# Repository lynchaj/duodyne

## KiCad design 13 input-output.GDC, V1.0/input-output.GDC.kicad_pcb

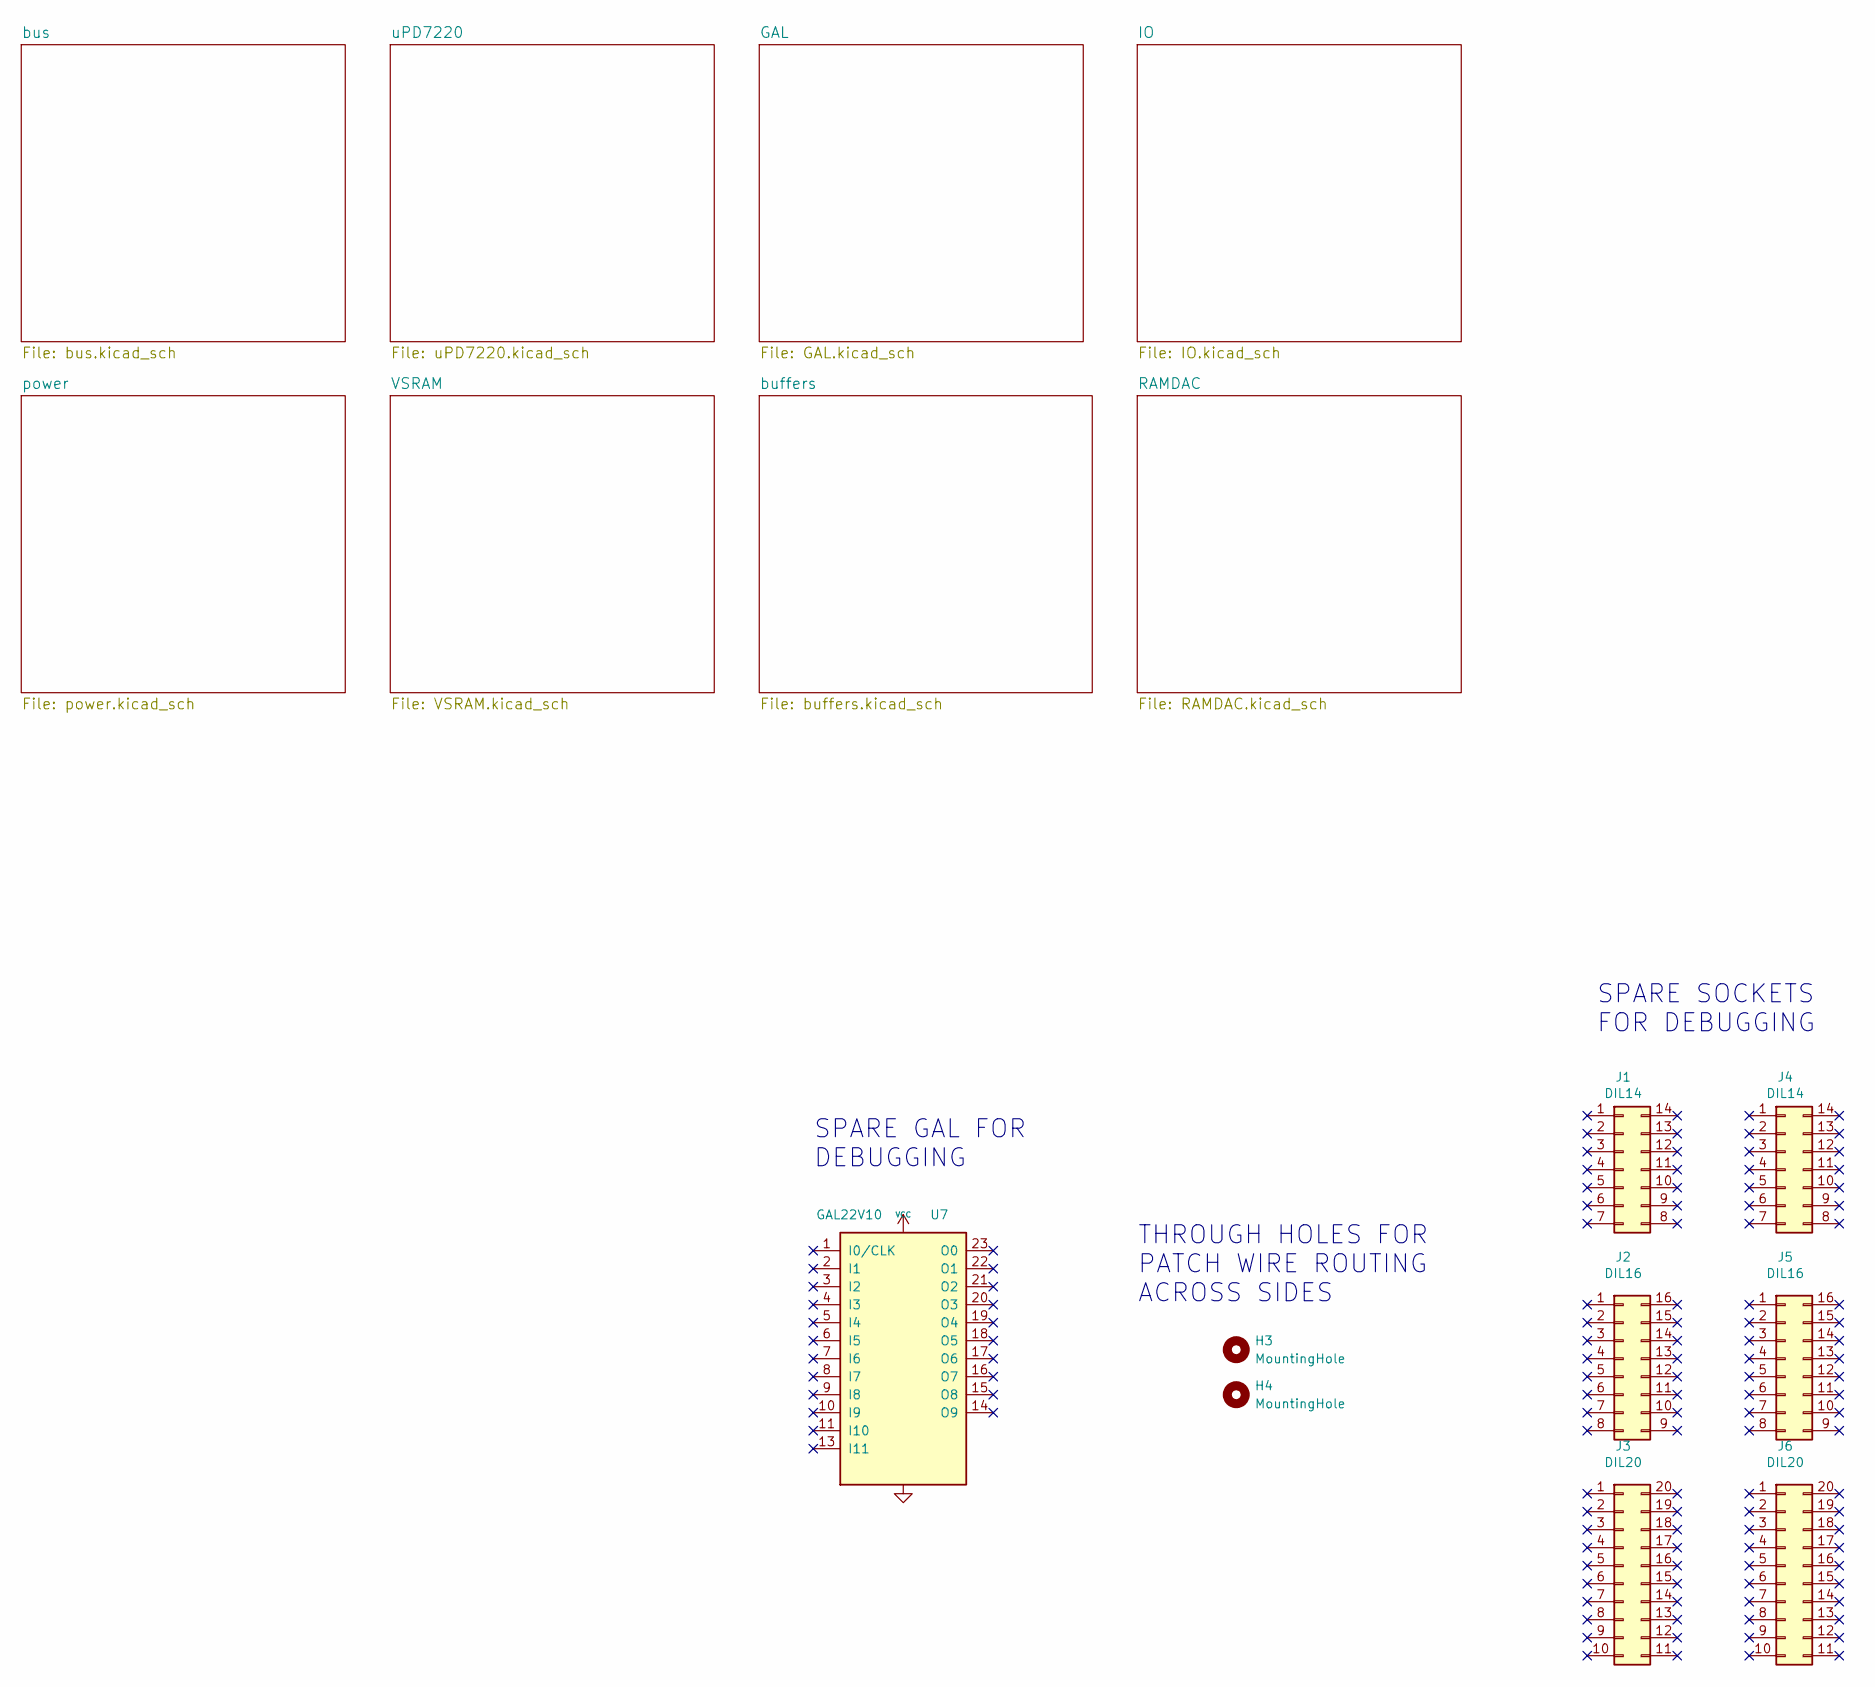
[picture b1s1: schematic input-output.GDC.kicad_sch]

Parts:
H3, H4: MountingHole; MountingHole_2.2mm_M2_DIN965_Pad
J1, J4: DIL14; DIP-14_W7.62mm_Socket
J2, J5: DIL16; DIP-16_W7.62mm_Socket
J3, J6: DIL20; DIP-20_W7.62mm_Socket
U7: GAL22V10; DIP-24_W7.62mm_Socket

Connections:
VCC: U7.24 (VCC); also elsewhere on the board

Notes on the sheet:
SPARE SOCKETS FOR DEBUGGING
SPARE GAL FOR DEBUGGING
THROUGH HOLES FOR PATCH WIRE ROUTING ACROSS SIDES

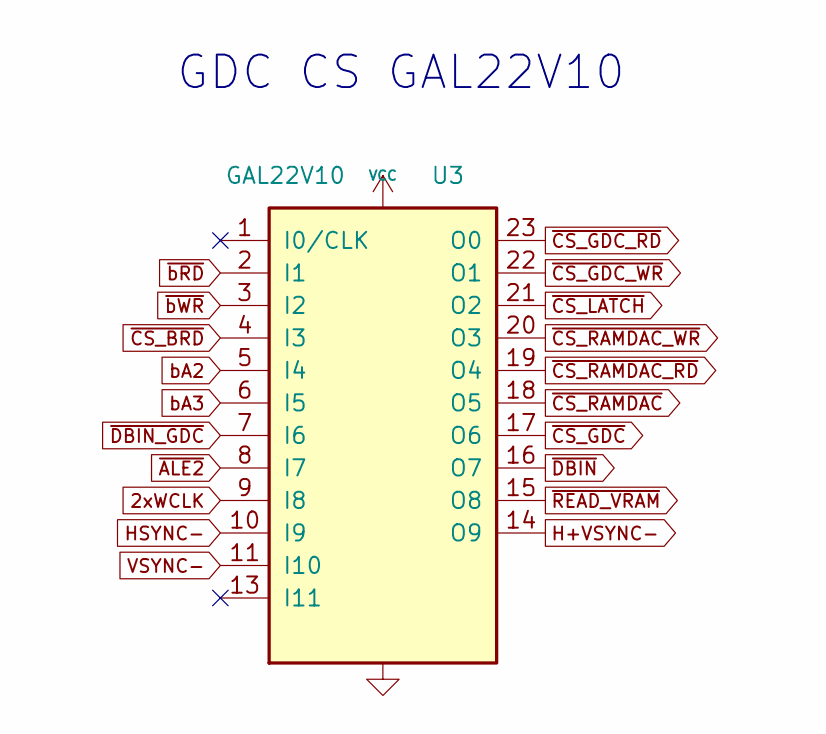
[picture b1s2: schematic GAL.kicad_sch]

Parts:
U3: GAL22V10; DIP-24_W7.62mm_Socket

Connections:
2xWCLK: U3.9 (I8); also elsewhere on the board
H+VSYNC-: U3.14 (O9); also elsewhere on the board
HSYNC-: U3.10 (I9); also elsewhere on the board
VCC: U3.24 (VCC); also elsewhere on the board
VSYNC-: U3.11 (I10); also elsewhere on the board
bA2: U3.5 (I4); also elsewhere on the board
bA3: U3.6 (I5); also elsewhere on the board
~ALE2: U3.8 (I7); also elsewhere on the board
~CS_BRD: U3.4 (I3); also elsewhere on the board
~CS_GDC_RD: U3.23 (O0); also elsewhere on the board
~CS_GDC_WR: U3.22 (O1); also elsewhere on the board
~CS_GDC: U3.17 (O6); also elsewhere on the board
~CS_LATCH: U3.21 (O2); also elsewhere on the board
~CS_RAMDAC_RD: U3.19 (O4); also elsewhere on the board
~CS_RAMDAC_WR: U3.20 (O3); also elsewhere on the board
~CS_RAMDAC: U3.18 (O5); also elsewhere on the board
~DBIN_GDC: U3.7 (I6); also elsewhere on the board
~DBIN: U3.16 (O7); also elsewhere on the board
~READ_VRAM: U3.15 (O8); also elsewhere on the board
~bRD: U3.2 (I1); also elsewhere on the board
~bWR: U3.3 (I2); also elsewhere on the board

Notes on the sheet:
GDC CS GAL22V10

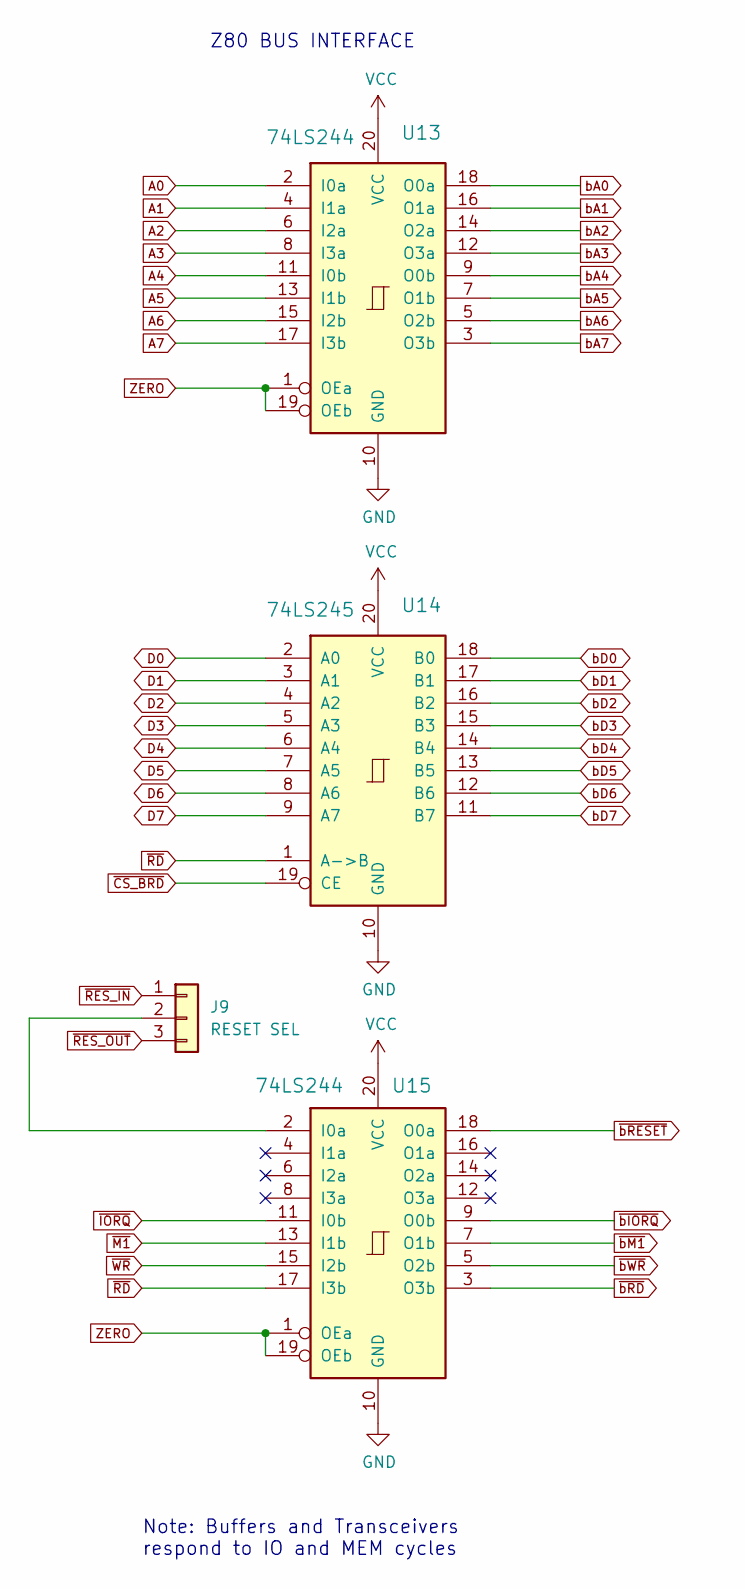
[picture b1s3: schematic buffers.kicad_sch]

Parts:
J9: RESET SEL; PinHeader_1x03_P2.54mm_Vertical
U13, U15: 74LS244; DIP-20_W7.62mm_Socket
U14: 74LS245; DIP-20_W7.62mm_Socket

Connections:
A0: U13.2 (I0a); also elsewhere on the board
A1: U13.4 (I1a); also elsewhere on the board
A2: U13.6 (I2a); also elsewhere on the board
A3: U13.8 (I3a); also elsewhere on the board
A4: U13.11 (I0b); also elsewhere on the board
A5: U13.13 (I1b); also elsewhere on the board
A6: U13.15 (I2b); also elsewhere on the board
A7: U13.17 (I3b); also elsewhere on the board
D0: U14.2 (A0); also elsewhere on the board
D1: U14.3 (A1); also elsewhere on the board
D2: U14.4 (A2); also elsewhere on the board
D3: U14.5 (A3); also elsewhere on the board
D4: U14.6 (A4); also elsewhere on the board
D5: U14.7 (A5); also elsewhere on the board
D6: U14.8 (A6); also elsewhere on the board
D7: U14.9 (A7); also elsewhere on the board
unnamed: J9.2, U15.2 (I0a)
VCC: U13.20 (VCC), U14.20 (VCC), U15.20 (VCC); also elsewhere on the board
ZERO: U13.1 (OEa), U13.19 (OEb), U15.1 (OEa), U15.19 (OEb); also elsewhere on the board
bA0: U13.18 (O0a); also elsewhere on the board
bA1: U13.16 (O1a); also elsewhere on the board
bA2: U13.14 (O2a); also elsewhere on the board
bA3: U13.12 (O3a); also elsewhere on the board
bA4: U13.9 (O0b); also elsewhere on the board
bA5: U13.7 (O1b); also elsewhere on the board
bA6: U13.5 (O2b); also elsewhere on the board
bA7: U13.3 (O3b); also elsewhere on the board
bD0: U14.18 (B0); also elsewhere on the board
bD1: U14.17 (B1); also elsewhere on the board
bD2: U14.16 (B2); also elsewhere on the board
bD3: U14.15 (B3); also elsewhere on the board
bD4: U14.14 (B4); also elsewhere on the board
bD5: U14.13 (B5); also elsewhere on the board
bD6: U14.12 (B6); also elsewhere on the board
bD7: U14.11 (B7); also elsewhere on the board
~CS_BRD: U14.19 (CE); also elsewhere on the board
~IORQ: U15.11 (I0b); also elsewhere on the board
~M1: U15.13 (I1b); also elsewhere on the board
~RD: U14.1 (A->B), U15.17 (I3b); also elsewhere on the board
~RES_IN: J9.1; also elsewhere on the board
~RES_OUT: J9.3; also elsewhere on the board
~WR: U15.15 (I2b); also elsewhere on the board
~bIORQ: U15.9 (O0b); also elsewhere on the board
~bM1: U15.7 (O1b); also elsewhere on the board
~bRD: U15.3 (O3b); also elsewhere on the board
~bRESET: U15.18 (O0a); also elsewhere on the board
~bWR: U15.5 (O2b); also elsewhere on the board

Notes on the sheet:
Z80 BUS INTERFACE
Note: Buffers and Transceivers respond to IO and MEM cycles

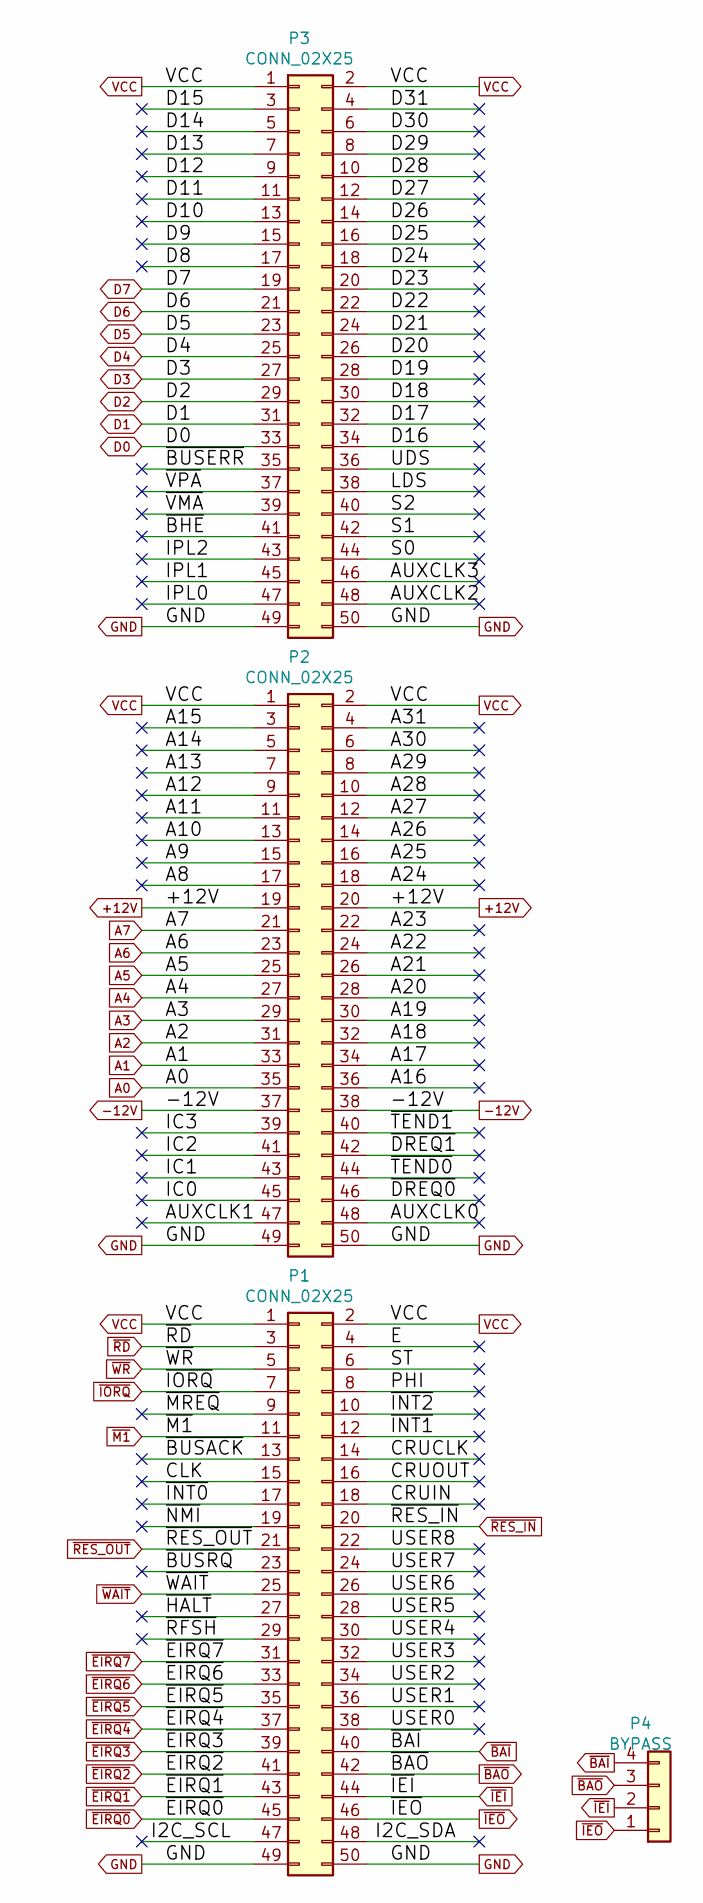
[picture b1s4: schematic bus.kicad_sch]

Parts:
P1, P2, P3: CONN_02X25; IDC-Header_2x25_P2.54mm_Horizontal
P4: BYPASS; PinHeader_1x04_P2.54mm_Vertical

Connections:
+12V: P2.19, P2.20
-12V: P2.37, P2.38
/bus/A8: P2.17
/bus/A9: P2.15
/bus/A10: P2.13
/bus/A11: P2.11
/bus/A12: P2.9
/bus/A13: P2.7
/bus/A14: P2.5
/bus/A15: P2.3
/bus/A16: P2.36
/bus/A17: P2.34
/bus/A18: P2.32
/bus/A19: P2.30
/bus/A20: P2.28
/bus/A21: P2.26
/bus/A22: P2.24
/bus/A23: P2.22
/bus/A24: P2.18
/bus/A25: P2.16
/bus/A26: P2.14
/bus/A27: P2.12
/bus/A28: P2.10
/bus/A29: P2.8
/bus/A30: P2.6
/bus/A31: P2.4
/bus/AUXCLK0: P2.48
/bus/AUXCLK1: P2.47
/bus/AUXCLK2: P3.48
/bus/AUXCLK3: P3.46
/bus/CLK: P1.15
/bus/CRUCLK: P1.14
/bus/CRUIN: P1.18
/bus/CRUOUT: P1.16
/bus/D8: P3.17
/bus/D9: P3.15
/bus/D10: P3.13
/bus/D11: P3.11
/bus/D12: P3.9
/bus/D13: P3.7
/bus/D14: P3.5
/bus/D15: P3.3
/bus/D16: P3.34
/bus/D17: P3.32
/bus/D18: P3.30
/bus/D19: P3.28
/bus/D20: P3.26
/bus/D21: P3.24
/bus/D22: P3.22
/bus/D23: P3.20
/bus/D24: P3.18
/bus/D25: P3.16
/bus/D26: P3.14
/bus/D27: P3.12
/bus/D28: P3.10
/bus/D29: P3.8
/bus/D30: P3.6
/bus/D31: P3.4
/bus/E: P1.4
/bus/I2C_SCL: P1.47
/bus/I2C_SDA: P1.48
/bus/IC0: P2.45
/bus/IC1: P2.43
/bus/IC2: P2.41
/bus/IC3: P2.39
/bus/IPL0: P3.47
/bus/IPL1: P3.45
/bus/IPL2: P3.43
/bus/LDS: P3.38
/bus/PHI: P1.8
/bus/S0: P3.44
/bus/S1: P3.42
/bus/S2: P3.40
/bus/ST: P1.6
/bus/UDS: P3.36
/bus/USER0: P1.38
/bus/USER1: P1.36
/bus/USER2: P1.34
/bus/USER3: P1.32
/bus/USER4: P1.30
/bus/USER5: P1.28
/bus/USER6: P1.26
/bus/USER7: P1.24
/bus/USER8: P1.22
/bus/~BHE: P3.41
/bus/~BUSACK: P1.13
/bus/~BUSERR: P3.35
/bus/~BUSRQ: P1.23
/bus/~EIRQ0: P1.45
/bus/~EIRQ1: P1.43
/bus/~EIRQ2: P1.41
/bus/~EIRQ3: P1.39
/bus/~EIRQ4: P1.37
/bus/~EIRQ5: P1.35
/bus/~EIRQ6: P1.33
/bus/~EIRQ7: P1.31
/bus/~HALT: P1.27
/bus/~INT0: P1.17
/bus/~INT1: P1.12
/bus/~INT2: P1.10
/bus/~MREQ: P1.9
/bus/~NMI: P1.19
/bus/~RFSH: P1.29
/bus/~VMA: P3.39
/bus/~VPA: P3.37
/bus/~WAIT: P1.25
A0: P2.35; also elsewhere on the board
A1: P2.33; also elsewhere on the board
A2: P2.31; also elsewhere on the board
A3: P2.29; also elsewhere on the board
A4: P2.27; also elsewhere on the board
A5: P2.25; also elsewhere on the board
A6: P2.23; also elsewhere on the board
A7: P2.21; also elsewhere on the board
D0: P3.33; also elsewhere on the board
D1: P3.31; also elsewhere on the board
D2: P3.29; also elsewhere on the board
D3: P3.27; also elsewhere on the board
D4: P3.25; also elsewhere on the board
D5: P3.23; also elsewhere on the board
D6: P3.21; also elsewhere on the board
D7: P3.19; also elsewhere on the board
VCC: P1.1, P1.2, P2.1, P2.2, P3.1, P3.2; also elsewhere on the board
~BAI: P1.40, P4.4
~BAO: P1.42, P4.3
~DREQ0: P2.46; also elsewhere on the board
~DREQ1: P2.42; also elsewhere on the board
~IEI: P1.44, P4.2
~IEO: P1.46, P4.1
~IORQ: P1.7; also elsewhere on the board
~M1: P1.11; also elsewhere on the board
~RD: P1.3; also elsewhere on the board
~RES_IN: P1.20; also elsewhere on the board
~RES_OUT: P1.21; also elsewhere on the board
~TEND0: P2.44; also elsewhere on the board
~TEND1: P2.40; also elsewhere on the board
~WR: P1.5; also elsewhere on the board

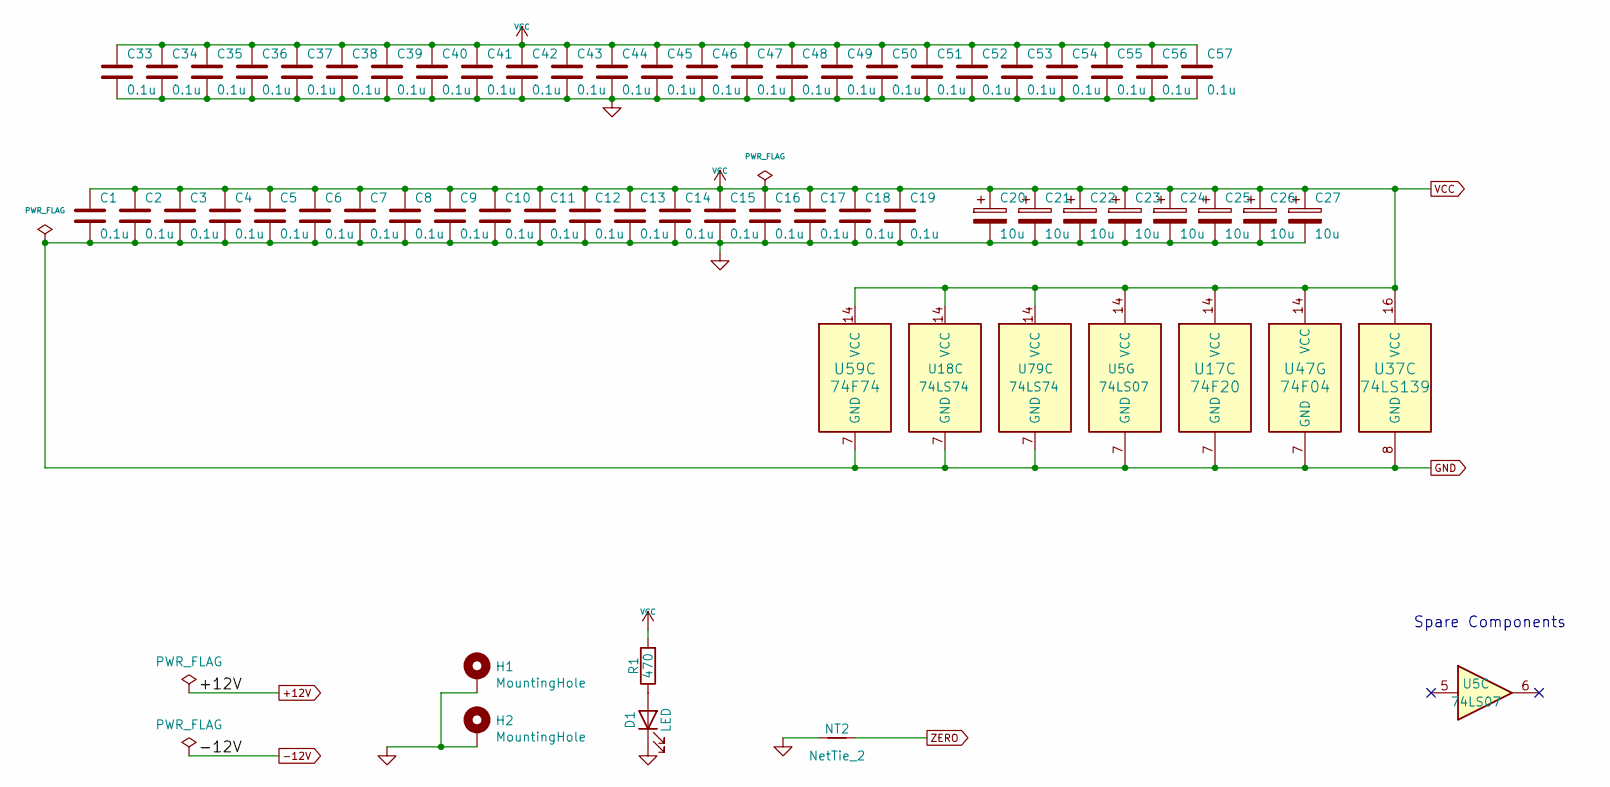
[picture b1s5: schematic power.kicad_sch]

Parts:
C1, C2, C3, C4, C5, C6, C7, C8, C9, C10, C11, C12, C13, C14, C15, C16, C17, C18, C19, C33, C34, C35, C36, C37, C38, C39, C40, C41, C42, C43, C44, C45, C46, C47, C48, C49, C50, C51, C52, C53, C54, C55, C56, C57: 0.1u; C_Disc_D5.0mm_W2.5mm_P5.00mm
C20, C21, C22, C23, C24, C25, C26, C27: 10u; CP_Radial_D5.0mm_P2.50mm
D1: LED; LED_D3.0mm_Horizontal_O3.81mm_Z2.0mm
H1, H2: MountingHole; MountingHole_3.2mm_M3_Pad
NT2: NetTie_2; NetTie-2_THT_Pad0.3mm
R1: 470; R_Axial_DIN0207_L6.3mm_D2.5mm_P7.62mm_Horizontal
U5: 74LS07; DIP-14_W7.62mm
U17: 74F20; DIP-14_W7.62mm
U18, U79: 74LS74; DIP-14_W7.62mm
U37: 74LS139; DIP-16_W7.62mm
U47: 74F04; DIP-14_W7.62mm
U59: 74F74; DIP-14_W7.62mm

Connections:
unnamed: D1.2 (A), R1.1
VCC: C1.1, C2.1, C3.1, C4.1, C5.1, C6.1, C7.1, C8.1, C9.1, C10.1, C11.1, C12.1, C13.1, C14.1, C15.1, C16.1, C17.1, C18.1, C19.1, C20.1, C21.1, C22.1, C23.1, C24.1, C25.1, C26.1, C27.1, C33.1, C34.1, C35.1, C36.1, C37.1, C38.1, C39.1, C40.1, C41.1, C42.1, C43.1, C44.1, C45.1, C46.1, C47.1, C48.1, C49.1, C50.1, C51.1, C52.1, C53.1, C54.1, C55.1, C56.1, C57.1, R1.2, U5.14 (VCC), U17.14 (VCC), U18.14 (VCC), U37.16 (VCC), U47.14 (VCC), U59.14 (VCC), U79.14 (VCC); also elsewhere on the board
ZERO: NT2.2; also elsewhere on the board

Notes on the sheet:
Spare Components

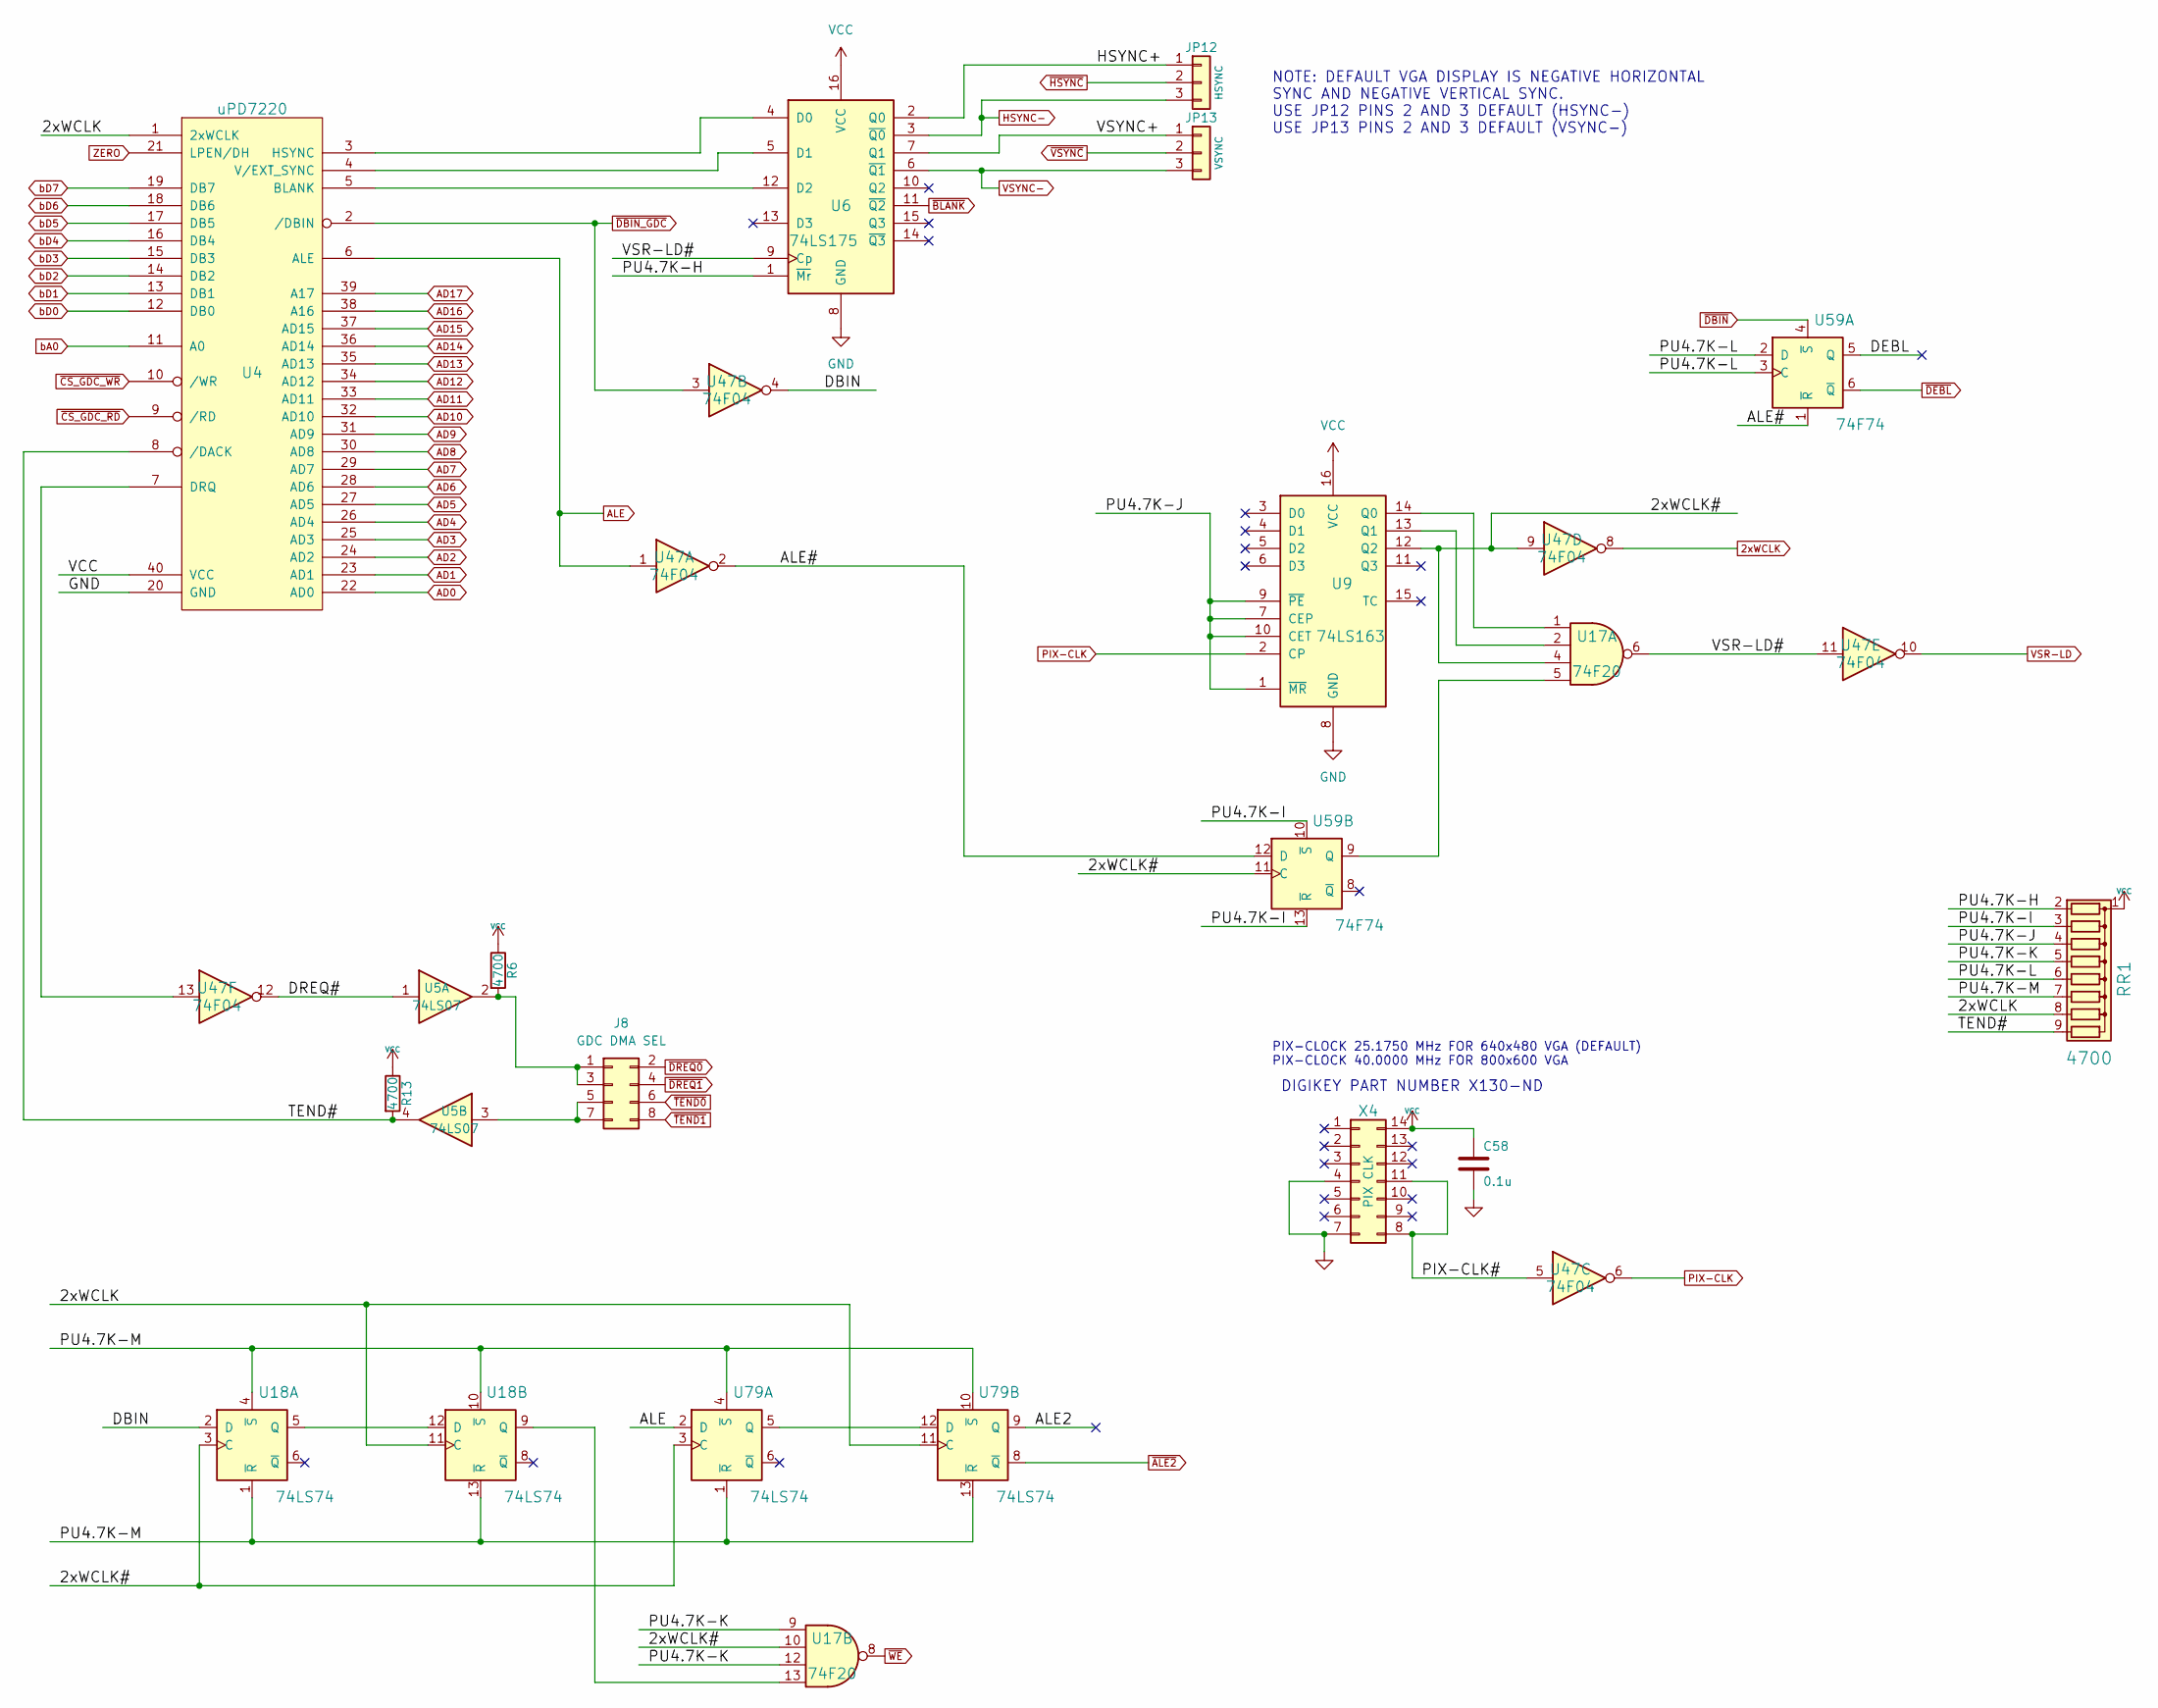
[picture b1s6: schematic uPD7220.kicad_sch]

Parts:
C58: 0.1u; C_Disc_D5.0mm_W2.5mm_P5.00mm
J8: GDC DMA SEL; PinHeader_2x04_P2.54mm_Vertical
JP12: HSYNC; PinHeader_1x03_P2.54mm_Vertical
JP13: VSYNC; PinHeader_1x03_P2.54mm_Vertical
R6, R13: 4700; R_Axial_DIN0207_L6.3mm_D2.5mm_P7.62mm_Horizontal
RR1: 4700; R_Array_SIP9
U4: uPD7220; DIP-40_W15.24mm_Socket
U5: 74LS07; DIP-14_W7.62mm_Socket
U6: 74LS175; DIP-16_W7.62mm_Socket
U9: 74LS163; DIP-16_W7.62mm_Socket
U17: 74F20; DIP-12_W7.62mm_Socket
U18, U79: 74LS74; DIP-14_W7.62mm_Socket
U47: 74F04; DIP-14_W7.62mm_Socket
U59: 74F74; DIP-14_W7.62mm_Socket
X4: PIX CLK; DIP-14_W7.62mm_Socket

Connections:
2xWCLK: RR1.8 (R7), U4.1 (2xWCLK), U18.11 (C), U47.8, U79.11 (C); also elsewhere on the board
/uPD7220/2xWCLK#: U9.12 (Q2), U17.4, U17.10, U18.3 (C), U47.9, U59.11 (C), U79.3 (C)
/uPD7220/ALE2: U79.9 (Q)
/uPD7220/ALE#: U47.2, U59.1 (~R), U59.12 (D)
/uPD7220/DBIN: U18.2 (D), U47.4
/uPD7220/DEBL: U59.5 (Q)
/uPD7220/DREQ#: U5.1, U47.12
/uPD7220/HSYNC+: JP12.1, U6.2 (Q0)
/uPD7220/PIX-CLK#: U47.5, X4.8, X4.11
/uPD7220/PU4.7K-H: RR1.2 (R1), U6.1 (~Mr)
/uPD7220/PU4.7K-I: RR1.3 (R2), U59.10 (~S), U59.13 (~R)
/uPD7220/PU4.7K-J: RR1.4 (R3), U9.1 (~MR), U9.7 (CEP), U9.9 (~PE), U9.10 (CET)
/uPD7220/PU4.7K-K: RR1.5 (R4), U17.9, U17.12
/uPD7220/PU4.7K-L: RR1.6 (R5), U59.2 (D), U59.3 (C)
/uPD7220/PU4.7K-M: RR1.7 (R6), U18.1 (~R), U18.4 (~S), U18.10 (~S), U18.13 (~R), U79.1 (~R), U79.4 (~S), U79.10 (~S), U79.13 (~R)
/uPD7220/TEND#: R13.2, RR1.9 (R8), U4.8 (/DACK), U5.4
/uPD7220/VSR-LD#: U6.9 (Cp), U17.6, U47.11
/uPD7220/VSYNC+: JP13.1, U6.7 (Q1)
AD0: U4.22 (AD0); also elsewhere on the board
AD1: U4.23 (AD1); also elsewhere on the board
AD2: U4.24 (AD2); also elsewhere on the board
AD3: U4.25 (AD3); also elsewhere on the board
AD4: U4.26 (AD4); also elsewhere on the board
AD5: U4.27 (AD5); also elsewhere on the board
AD6: U4.28 (AD6); also elsewhere on the board
AD7: U4.29 (AD7); also elsewhere on the board
AD8: U4.30 (AD8); also elsewhere on the board
AD9: U4.31 (AD9); also elsewhere on the board
AD10: U4.32 (AD10); also elsewhere on the board
AD11: U4.33 (AD11); also elsewhere on the board
AD12: U4.34 (AD12); also elsewhere on the board
AD13: U4.35 (AD13); also elsewhere on the board
AD14: U4.36 (AD14); also elsewhere on the board
AD15: U4.37 (AD15); also elsewhere on the board
AD16: U4.38 (A16); also elsewhere on the board
AD17: U4.39 (A17); also elsewhere on the board
ALE: U4.6 (ALE), U47.1, U79.2 (D); also elsewhere on the board
HSYNC-: JP12.3, U6.3 (~Q0); also elsewhere on the board
unnamed: J8.1, J8.3, R6.2, U5.2
unnamed: J8.5, J8.7, U5.3
unnamed: U4.3 (HSYNC), U6.4 (D0)
unnamed: U4.4 (V/EXT_SYNC), U6.5 (D1)
unnamed: U4.5 (BLANK), U6.12 (D2)
unnamed: U4.7 (DRQ), U47.13
unnamed: U9.14 (Q0), U17.1
unnamed: U9.13 (Q1), U17.2
unnamed: U17.5, U59.9 (Q)
unnamed: U17.13, U18.9 (Q)
unnamed: U18.5 (Q), U18.12 (D)
unnamed: U79.5 (Q), U79.12 (D)
PIX-CLK: U9.2 (CP), U47.6; also elsewhere on the board
VCC: C58.1, R6.1, R13.1, RR1.1 (common), U4.40 (VCC), U6.16 (VCC), U9.16 (VCC), X4.14; also elsewhere on the board
VSR-LD: U47.10; also elsewhere on the board
VSYNC-: JP13.3, U6.6 (~Q1); also elsewhere on the board
ZERO: U4.21 (LPEN/DH); also elsewhere on the board
bA0: U4.11 (A0); also elsewhere on the board
bD0: U4.12 (DB0); also elsewhere on the board
bD1: U4.13 (DB1); also elsewhere on the board
bD2: U4.14 (DB2); also elsewhere on the board
bD3: U4.15 (DB3); also elsewhere on the board
bD4: U4.16 (DB4); also elsewhere on the board
bD5: U4.17 (DB5); also elsewhere on the board
bD6: U4.18 (DB6); also elsewhere on the board
bD7: U4.19 (DB7); also elsewhere on the board
~ALE2: U79.8 (~Q); also elsewhere on the board
~BLANK: U6.11 (~Q2); also elsewhere on the board
~CS_GDC_RD: U4.9 (/RD); also elsewhere on the board
~CS_GDC_WR: U4.10 (/WR); also elsewhere on the board
~DBIN_GDC: U4.2 (/DBIN), U47.3; also elsewhere on the board
~DBIN: U59.4 (~S); also elsewhere on the board
~DEBL: U59.6 (~Q); also elsewhere on the board
~DREQ0: J8.2; also elsewhere on the board
~DREQ1: J8.4; also elsewhere on the board
~HSYNC: JP12.2; also elsewhere on the board
~TEND0: J8.6; also elsewhere on the board
~TEND1: J8.8; also elsewhere on the board
~VSYNC: JP13.2; also elsewhere on the board
~WE: U17.8; also elsewhere on the board

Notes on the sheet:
NOTE: DEFAULT VGA DISPLAY IS NEGATIVE HORIZONTAL SYNC AND NEGATIVE VERTICAL SYNC. USE JP12 PINS 2 AND 3 DEFAULT (HSYNC-) USE JP13 PINS 2 AND 3 DEFAULT (VSYNC-)
DIGIKEY PART NUMBER X130-ND
PIX-CLOCK 25.1750 MHz FOR 640x480 VGA (DEFAULT) PIX-CLOCK 40.0000 MHz FOR 800x600 VGA
